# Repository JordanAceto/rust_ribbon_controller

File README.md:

# Rust Language STM32L412 Ribbon Controller

## Features

### Three analog outputs
- `RIBBON CV`: 1volt/per octave scaled control voltage generated by the main ribbon
- `GATE`: 5 volt gate signal which is high when pressing the main ribbon and low otherwise
- `MOD CV`: mod-wheel like control voltage generated by the MOD ribbon, in `[0v, +5v]` 

### MIDI output
- Note on/off based on finger position on the ribbon
- Pitch-bend message bends the pitch when the ribbon is in between notes 
- Mod: mod-wheel message generated by the MOD ribbon

### Three pitch modes are available
1) `QUANTIZE`: notes are forced to be musical half steps, sliding around will zipper to new notes
2) `ASSIST`: when you first press a new note it is forced to be a musical half step, but continued sliding is smooth
3) `SMOOTH`: no quantization is performed, offers the greatest degree of pitch freedom but is difficult to play in tune

### Glide control
- Adds portamento to the `RIBBON CV` signal
- This allows you to smooth out the steps when in `QUANTIZE` mode

### Notes about the MIDI output
- This software assumes that the pitch bend range on the receiving instrument is set to +/- 2 semitones (this is typically the default)
    - If the Assist or Smooth modes seem crazy, make sure that the pitch bend range on your instrument is set to +/- 2 semitones
- The MIDI output signal sends note-on, note-off, and pitch bend messages to generate the smooth ribbon action
    - This works best with a mono instrument, and may act differently depending on the MIDI implementation of the receiving device
    - If the receiving instrument has non-retriggering envelopes, it will smoothly slide as expected
    - If the instrument has retriggering envelopes, each time you slide into a new note the envelopes will be triggered
- The MIDI output starts on a fairly low note
    - It works best if the instrument being controlled can be transposed to different octaves

### Rear panel IO jacks and controls
- Output jacks for analog signals `RIBBON CV`, `MOD CV`, and `GATE`
- Standard `MIDI OUT` 5 pin DIN output jack
- `MIDI CH` channel select rotary switch
    - MIDI output is sent on the channel set here
- `9VDC IN` power supply input jack

## Calibration
- A trim potentiometer is exposed through a small hole so the device may be calibrated without disassembly
- Measure the `RIBBON CV` signal with a multimeter
- Set the `MODE` switch to `QUANTIZE`
- Adjust the trim potentiometer while playing alternating octaves so that the octaves are as close to 1.000v apart as you can get
- The `MOD CV` and MIDI output do not require calibration

## Power supply
- A common guitar-pedal style center-negative 9 volt DC wall wart powers the device
- The circuit consumes approximately 20mA from the 9 volt DC power supply

## Project status
- A prototype has been built and tested
- A handmade wooden body houses the components and provides a comfortable wrist rest while playing

## Project goals
- Mostly just for fun and to explore embedded Rust
- Serve as a test bed for the [Josh Ox Ribbon Synth](https://github.com/JordanAceto/josh_Ox_ribbon_synth)
- Build a cute little CV and MIDI source

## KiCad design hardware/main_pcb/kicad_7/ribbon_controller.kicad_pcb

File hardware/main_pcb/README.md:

# main_pcb

## ribbon_controller

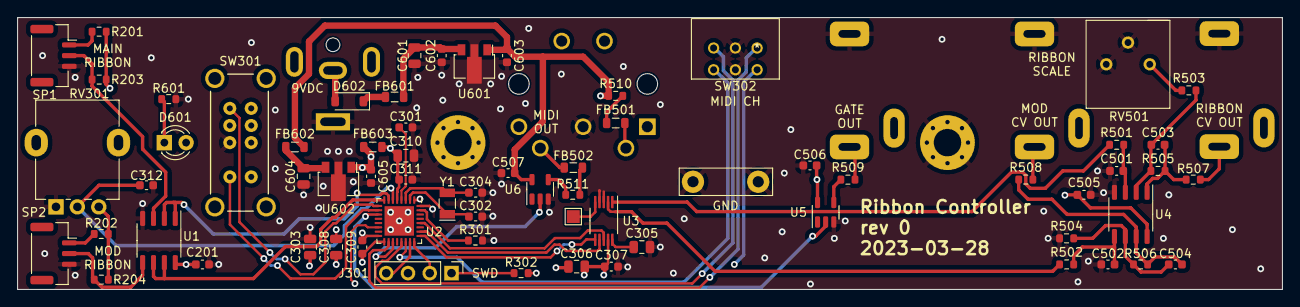
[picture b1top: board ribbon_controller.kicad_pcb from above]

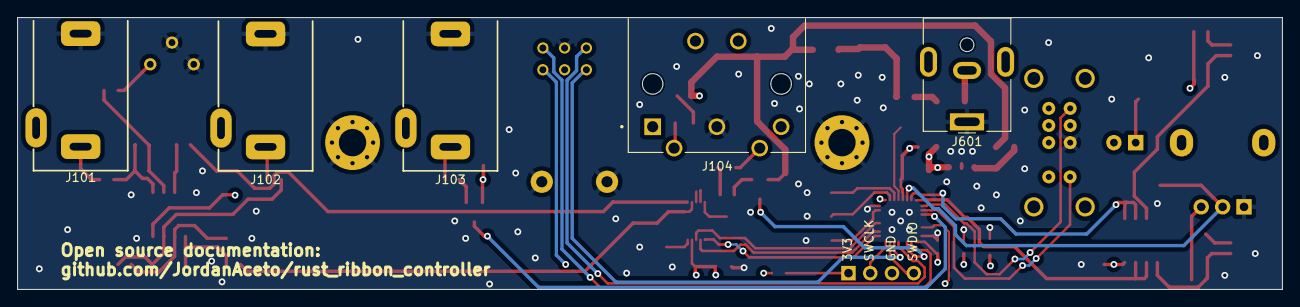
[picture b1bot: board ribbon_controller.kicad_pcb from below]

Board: 4 copper layers, 147.7 x 31.8 mm, 75 parts (5 on the bottom side), 54 nets.

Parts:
C201, C301, C307, C309, C311, C312, C501, C502, C503, C504, C505, C506, C507, C602, C603, C605: 100n; C_0603_1608Metric
C302, C304: 4p3; C_0603_1608Metric
C303: 10u; C_0805_2012Metric
C305, C306, C308, C310: 1u; C_0805_2012Metric
C601, C604: 2u2; C_0805_2012Metric
D601: XLMDK65D; LED_D3.0mm
D602: B5819W; D_SOD-123
FB501, FB502: 600R @ 100MHz; L_0805_2012Metric
FB601, FB602, FB603: 100R @ 100MHz; L_0805_2012Metric
H601, H602: MountingHole_Pad; MountingHole_3.2mm_M3_Pad_Via
J101, J102, J103: PJ302M
J104: CUI_SDF-50J
J301: SWD_header; PinHeader_1x04_P2.54mm_Vertical
J601: CUI_PJ-063AH; BarrelJack_CUI_PJ-063AH_Horizontal
R201, R202, R301, R501, R502, R504, R505, R506, R601: 10k; R_0603_1608Metric
R203, R204: 1M; R_0603_1608Metric
R302, R507, R510, R511: 220; R_0603_1608Metric
R503: 9k1; R_0603_1608Metric
R508, R509: 1k; R_0603_1608Metric
RV301: 10k; Potentiometer_Alpha_RD901F-40-00D_Single_Vertical
RV501: 2k; Potentiometer_Bourns_3296P_Horizontal
SP1: 400mm_softpot; JST_GH_SM03B-GHS-TB_1x03-1MP_P1.25mm_Horizontal
SP2: 50mm_softpot; JST_GH_SM03B-GHS-TB_1x03-1MP_P1.25mm_Horizontal
SW301: E-Switch_EG2301
SW302: nidec_SD-1011; SD-1011
TP401: ~{CLR}; TestPoint_Pad_1.5x1.5mm
TP601: GND; TestPoint_Bridge_Pitch7.62mm_Drill1.3mm
U1, U4: MCP6002-xSN; SO-8_3.9x4.9mm_P1.27mm
U2: STM32L412K8Ux; QFN-32-1EP_5x5mm_P0.5mm_EP3.45x3.45mm
U3: DAC8162xDGSx; VSSOP-10_3x3mm_P0.5mm
U5, U6: SN74LV1T34DBV; SOT-23-5
U601: L78L05_SOT89; SOT-89-3
U602: L78L33_SOT89; SOT-89-3
Y1: 32_768KHZ; Crystal_SMD_MicroCrystal_CC7V-T1A-2Pin_3.2x1.5mm

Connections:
+3.3V: C303.1, C306.1, C307.1, C308.1, C309.1, C605.1, FB603.1, R302.1, U2.1 (VDD), U2.17 (VDD), U3.9 (AVDD), U602.1 (OUT)
+3.3VA: C201.1, C310.1, C311.1, FB603.2, R201.1, R202.1, R203.1, R204.1, RV301.3, U1.8 (V+), U2.5 (VDDA)
+5V: C505.1, C506.1, C507.1, C603.1, FB602.1, R510.1, U4.8 (V+), U5.5 (VCC), U6.5 (VCC), U601.1 (OUT)
+9V: C601.1, C602.1, FB601.2, U601.3 (IN)
/DAC/MOD_CV_2V5: R502.1, U3.2 (VOUTB)
/DAC/RIBBON_CV_2V5: R501.1, U3.1 (VOUTA)
/DAC/SPI_CS: U2.25 (PA15), U3.6 (~SYNC)
/DAC/SPI_SCK: U2.26 (PB3), U3.7 (SCLK)
/DAC/SPI_SDO: U2.28 (PB5), U3.8 (DIN)
/input_buffers/MAIN_RIB_RAW_V: U1.1, U1.2 (-), U2.7 (PA1)
/input_buffers/MOD_RIB_RAW_V: U1.6 (-), U1.7, U2.8 (PA2)
/microcontroller/GATE_3V3: U2.11 (PA5), U5.2 (A)
/microcontroller/GLIDE_CV: C312.1, RV301.2, U2.6 (PA0)
/microcontroller/MIDI_CH_1: SW302.1, U2.18 (PA8)
/microcontroller/MIDI_CH_2: SW302.2, U2.22 (PA12)
/microcontroller/MIDI_CH_4: SW302.4, U2.21 (PA11)
/microcontroller/MIDI_CH_8: SW302.8, U2.14 (PB0)
/microcontroller/MIDI_TX_3V3: U2.19 (PA9), U6.2 (A)
/microcontroller/MODE_SW_1: SW301.1, U2.9 (PA3)
/microcontroller/MODE_SW_2: SW301.4, U2.10 (PA4)
/microcontroller/SYS_SWCLK: J301.2, U2.24 (PA14)
/microcontroller/SYS_SWDIO: J301.4, U2.23 (PA13)
/output_buffers/GATE_5V: J103.T, R509.2
/output_buffers/MIDI_OUT_P4: FB501.2, J104.4
/output_buffers/MIDI_OUT_P5: FB502.2, J104.5
/output_buffers/MOD_CV_5V: J102.T, R508.2
/output_buffers/RIBBON_CV_FINAL: J101.T, R507.2
GND: C201.2, C301.1, C302.1, C303.2, C304.1, C305.2, C306.2, C307.2, C308.2, C309.2, C310.2, C311.2, C312.2, C501.1, C502.1, C505.2, C506.2, C507.2, C601.2, C602.2, C603.2, C604.2, C605.2, H601.1, H602.1, J101.S, J102.S, J103.S, J104.2, J301.3, J601.1, R301.1, R504.1, R601.1, RV301.1, RV501.2, RV501.3, SP1.3, SP2.3, SW301.3, SW302.C, TP601.1, U1.4 (V-), U2.16 (VSS), U2.32 (VSS), U2.33 (VSS), U3.3 (GND), U3.4 (~LDAC), U4.4 (V-), U5.3 (GND), U6.3 (GND), U601.2 (GND), U602.2 (GND)
unnamed: C503.2, R505.2, R507.1, U4.1
unnamed: C504.2, R506.2, R508.1, U4.7
unnamed: D601.2 (A), D602.2 (A), J601.2
unnamed: D601.1 (K), R601.2
unnamed: D602.1 (K), FB601.1
unnamed: FB501.1, R510.2
unnamed: FB502.1, R511.2
unnamed: J301.1, R302.2
unnamed: R201.2, SP1.1
unnamed: R202.2, SP2.1
unnamed: R503.1, RV501.1
unnamed: R203.2, SP1.2, U1.3 (+)
unnamed: R204.2, SP2.2, U1.5 (+)
unnamed: C301.2, U2.4 (NRST)
unnamed: C302.2, U2.2 (PC14), Y1.1
unnamed: C304.2, U2.3 (PC15), Y1.2
unnamed: R301.2, U2.31 (PH3)
unnamed: C305.1, U3.10 (VREFH/VREFOUT)
unnamed: TP401.1, U3.5 (~CLR)
unnamed: C501.2, R501.2, U4.3 (+)
unnamed: C503.1, R503.2, R505.1, U4.2 (-)
unnamed: C502.2, R502.2, U4.5 (+)
unnamed: C504.1, R504.2, R506.1, U4.6 (-)
unnamed: R509.1, U5.4 (Y)
unnamed: R511.1, U6.4 (Y)
unnamed: C604.1, FB602.2, U602.3 (IN)

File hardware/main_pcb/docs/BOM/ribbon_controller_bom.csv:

"#","Reference","Qty","Value","Footprint","DNP"
"1","C201, C301, C307, C309, C311, C312, C501, C502, C503, C504, C505, C506, C507, C602, C603, C605","16","100n","Capacitor_SMD:C_0603_1608Metric",""
"2","C302, C304","2","4p3","Capacitor_SMD:C_0603_1608Metric",""
"3","C303","1","10u","Capacitor_SMD:C_0805_2012Metric",""
"4","C305, C306, C308, C310","4","1u","Capacitor_SMD:C_0805_2012Metric",""
"5","C601, C604","2","2u2","Capacitor_SMD:C_0805_2012Metric",""
"6","D601","1","XLMDK65D","LED_THT:LED_D3.0mm",""
"7","D602","1","B5819W","Diode_SMD:D_SOD-123",""
"8","FB501, FB502","2","600R @ 100MHz","Inductor_SMD:L_0805_2012Metric",""
"9","FB601, FB602, FB603","3","100R @ 100MHz","Inductor_SMD:L_0805_2012Metric",""
"10","H601, H602","2","MountingHole_Pad","MountingHole:MountingHole_3.2mm_M3_Pad_Via",""
"11","J101, J102, J103","3","PJ302M","custom_footprints:PJ302M",""
"12","J104","1","CUI_SDF-50J","custom_footprints:CUI_SDF-50J",""
"13","J301","1","SWD_header","Connector_PinHeader_2.54mm:PinHeader_1x04_P2.54mm_Vertical",""
"14","J601","1","CUI_PJ-063AH","Connector_BarrelJack:BarrelJack_CUI_PJ-063AH_Horizontal",""
"15","R201, R202, R301, R501, R502, R504, R505, R506, R601","9","10k","Resistor_SMD:R_0603_1608Metric",""
"16","R203, R204","2","1M","Resistor_SMD:R_0603_1608Metric",""
"17","R302, R507, R510, R511","4","220","Resistor_SMD:R_0603_1608Metric",""
"18","R503","1","9k1","Resistor_SMD:R_0603_1608Metric",""
"19","R508, R509","2","1k","Resistor_SMD:R_0603_1608Metric",""
"20","RV301","1","10k ","custom_footprints:Potentiometer_Alpha_RD901F-40-00D_Single_Vertical",""
"21","RV501","1","2k","custom_footprints:Potentiometer_Bourns_3296P_Horizontal",""
"22","SP1","1","400mm_softpot","Connector_JST:JST_GH_SM03B-GHS-TB_1x03-1MP_P1.25mm_Horizontal",""
"23","SP2","1","50mm_softpot","Connector_JST:JST_GH_SM03B-GHS-TB_1x03-1MP_P1.25mm_Horizontal",""
"24","SW301","1","E-Switch_EG2301","custom_footprints:E-Switch_EG2301",""
"25","SW302","1","nidec_SD-1011","custom_footprints:SD-1011",""
"26","TP401","1","~{CLR}","TestPoint:TestPoint_Pad_1.5x1.5mm",""
"27","TP601","1","GND","TestPoint:TestPoint_Bridge_Pitch7.62mm_Drill1.3mm",""
"28","U1, U4","2","MCP6002-xSN","Package_SO:SO-8_3.9x4.9mm_P1.27mm",""
"29","U2","1","STM32L412K8Ux","Package_DFN_QFN:QFN-32-1EP_5x5mm_P0.5mm_EP3.45x3.45mm",""
"30","U3","1","DAC8162xDGSx","Package_SO:VSSOP-10_3x3mm_P0.5mm",""
"31","U5, U6","2","SN74LV1T34DBV","Package_TO_SOT_SMD:SOT-23-5",""
"32","U601","1","L78L05_SOT89","Package_TO_SOT_SMD:SOT-89-3",""
"33","U602","1","L78L33_SOT89","Package_TO_SOT_SMD:SOT-89-3",""
"34","Y1","1","32_768KHZ","Crystal:Crystal_SMD_MicroCrystal_CC7V-T1A-2Pin_3.2x1.5mm",""

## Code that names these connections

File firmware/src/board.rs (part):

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        // Gate pin
        //
        ////////////////////////////////////////////////////////////////////////
        let gate_pin = gpioa.pa5.into_push_pull_output_in_state(
            &mut gpioa.moder,
            &mut gpioa.otyper,
            PinState::Low,
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
        // gpio pins which are configured as analog inputs on the physical PCB
        let mut adc_pins = (
            gpioa.pa0.into_analog(&mut gpioa.moder, &mut gpioa.pupdr),
            gpioa.pa1.into_analog(&mut gpioa.moder, &mut gpioa.pupdr),
            gpioa.pa2.into_analog(&mut gpioa.moder, &mut gpioa.pupdr),
        );
        adc1.configure_sequence(&mut adc_pins.0, Sequence::One, SampleTime::Cycles640_5);
        adc1.configure_sequence(&mut adc_pins.1, Sequence::Two, SampleTime::Cycles640_5);
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        }

        let tx_pin = gpioa
            .pa9
            .into_alternate(&mut gpioa.moder, &mut gpioa.otyper, &mut gpioa.afrh);
        let rx_pin =
            gpioa
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        //
        ////////////////////////////////////////////////////////////////////////
        let sck = gpiob
            .pb3
            .into_alternate(&mut gpiob.moder, &mut gpiob.otyper, &mut gpiob.afrl);
        let sdi = gpiob
            .pb4
            .into_alternate(&mut gpiob.moder, &mut gpiob.otyper, &mut gpiob.afrl);
        let sdo = gpiob
            .pb5
            .into_alternate(&mut gpiob.moder, &mut gpiob.otyper, &mut gpiob.afrl);

        let mut nss = gpioa.pa15.into_push_pull_output_in_state(
            &mut gpioa.moder,
            &mut gpioa.otyper,
            PinState::High,
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        ////////////////////////////////////////////////////////////////////////
        let mode_switch = (
            gpioa
                .pa3
                .into_pull_up_input(&mut gpioa.moder, &mut gpioa.pupdr),
            gpioa
                .pa4
                .into_pull_up_input(&mut gpioa.moder, &mut gpioa.pupdr),
        );

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        ////////////////////////////////////////////////////////////////////////
        let midi_ch_switch = (
            gpioa
                .pa8
                .into_pull_up_input(&mut gpioa.moder, &mut gpioa.pupdr),
            gpioa
                .pa12
                .into_pull_up_input(&mut gpioa.moder, &mut gpioa.pupdr),
            gpioa
                .pa11
                .into_pull_up_input(&mut gpioa.moder, &mut gpioa.pupdr),
            gpiob
                .pb0
                .into_pull_up_input(&mut gpiob.moder, &mut gpiob.pupdr),
        );

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/// Pins which may be read by the ADC are represented here
#[derive(Clone, Copy)]
pub enum AdcPin {
    PA0 = 0,
    PA1 = 1,
    PA2 = 2,
}

/// Channels of the onboard DAC are represented here
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
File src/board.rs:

use stm32l0xx_hal::{
    adc::{Adc, Ready},
    delay::Delay,
    gpio::{
        gpioa::{PA0, PA4, PA5, PA7, PA9},
        gpioc::{PC14, PC15},
        Analog, Input, Output, PullUp, PushPull,
    },
    pac::{Peripherals, ADC, SPI1},
    prelude::*,
    rcc, serial,
    spi::{NoMiso, Spi, MODE_0},
};

use nb::block;

/// The physical board hardware structure is represented here.
///
/// The board consists of digital and analog peripherals.
pub struct Board {
    /// The analog to digital converter
    adc: Adc<Ready>,

    /// The pin used to read analog signals via the ADC
    adc_pin: PA0<Analog>,

    /// GPIO pin used as a gate ouptut
    gate_pin: PA9<Output<PushPull>>,

    mode_switch_1: PC14<Input<PullUp>>,
    mode_switch_2: PC15<Input<PullUp>>,

    /// SPI peripheral for writing to onboard DAC
    spi: Spi<SPI1, (PA5<Analog>, NoMiso, PA7<Analog>)>,
    /// SPI chip select pin
    nss: PA4<Output<PushPull>>,

    /// The USART
    tx: serial::Tx<serial::USART2>,

    delay: Delay,
}

/// The channels of the MCP4822 DAC are represented here.
#[derive(Clone, Copy)]
pub enum Mcp4822Channel {
    A = 0,
    B = 1,
}

impl Board {
    /// `Board::init()` is the board with all necessary peripherals initialized.
    pub fn init() -> Self {
        // general peripheral housekeeping
        let dp = Peripherals::take().unwrap();
        let cp = cortex_m::Peripherals::take().unwrap();
        let mut rcc = dp.RCC.freeze(rcc::Config::hsi16());
        let gpioa = dp.GPIOA.split(&mut rcc);
        let gpioc = dp.GPIOC.split(&mut rcc);

        // mode switch pins
        let mode_switch_1 = gpioc.pc14.into_pull_up_input();
        let mode_switch_2 = gpioc.pc15.into_pull_up_input();

        // USART for MIDI output
        let tx_pin = gpioa.pa2;
        let rx_pin = gpioa.pa3;

        let usart = dp
            .USART2
            .usart(
                tx_pin,
                rx_pin,
                serial::Config {
                    baudrate: 31_250_u32.Bd(), // MIDI baud rate
                    wordlength: serial::WordLength::DataBits8,
                    parity: serial::Parity::ParityNone,
                    stopbits: serial::StopBits::STOP1,
                },
                &mut rcc,
            )
            .unwrap();

        let (tx, _) = usart.split();

        // ADC
        let adc = dp.ADC.constrain(&mut rcc);
        let adc_pin = gpioa.pa0.into_analog();
        // configure hardware oversampling for effective ADC resolution of 16 bits
        unsafe {
            (*ADC::ptr()).cfgr2.modify(|_, w| {
                w.ovsr().mul256();
                w.ovss().bits(4);
                w.ovse().enabled()
            });
        }

        // SPI DAC
        let mut nss = gpioa.pa4.into_push_pull_output();
        nss.set_high().unwrap();
        let sck = gpioa.pa5;
        let mosi = gpioa.pa7;

        let spi = dp
            .SPI1
            .spi((sck, NoMiso, mosi), MODE_0, 100_000.Hz(), &mut rcc);

        // GATE PIN
        let gate_pin = gpioa.pa9.into_push_pull_output();

        let delay = cp.SYST.delay(rcc.clocks);

        Self {
            adc,
            adc_pin,
            gate_pin,
            mode_switch_1,
            mode_switch_2,
            spi,
            nss,
            tx,
            delay,
        }
    }

    /// `board.sleep_ms(ms)` causes the board to busy-wait for the `ms` milliseconds
    pub fn sleep_ms(&mut self, ms: u16) {
        self.delay.delay_ms(ms);
    }

    /// `board.serial_write(val)` writes the byte `val` via the USART in a blocking fashion
    pub fn serial_write(&mut self, val: u8) {
        block!(self.tx.write(val)).ok();
    }

    /// `board.get_raw_adc()` is the current value of the ADC.
    pub fn get_raw_adc(&mut self) -> u16 {
        self.adc.read(&mut self.adc_pin).unwrap()
    }

    /// `board.get_mode_switch_1()` is the current state of mode switch 1
    pub fn get_mode_switch_1(&self) -> bool {
        self.mode_switch_1.is_low().unwrap()
    }

    /// `board.get_mode_switch_2()` is the current state of mode switch 2
    pub fn get_mode_switch_2(&self) -> bool {
        self.mode_switch_2.is_low().unwrap()
    }
    /// `board.mcp4822_write(val_u12, channel)` writes the 12 bit value to the given channel of the onboard MCP4822 DAC.
    ///
    /// # Arguments:
    ///
    /// * `val_u12` - The 12 bit unsigned value to write. Bits above 11 are trucated.
    ///
    /// * `channel` - The enumerated MCP4822 channel
    pub fn mcp4822_write(&mut self, val_u12: u16, channel: Mcp4822Channel) {
        let low_word = (val_u12 & 0xFF) as u8;

        // OR in the channel, GAIN=1x, and Enable Vout
        let high_word = (((val_u12 & DAC_MAX) >> 8) as u8) | ((channel as u8) << 7) | 0b00110000;

        self.nss.set_low().unwrap();
        self.spi.write(&[high_word, low_word]).unwrap();
        self.nss.set_high().unwrap();
    }

    /// `board.set_gate(val)` sets the state of the gate pin to `val`.
    pub fn set_gate(&mut self, val: bool) {
        match val {
            true => self.gate_pin.set_high().unwrap(),
            false => self.gate_pin.set_low().unwrap(),
        }
    }
}

/// The maximum value that can be produced by the Analog to Digital Converters.
pub const ADC_MAX: u16 = u16::MAX;

/// The maximum value that can be written to the onboard Digital to Analog Converter.
pub const DAC_MAX: u16 = 0x0FFF;

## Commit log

2022-12-21 Add license
2022-12-22 Enable ADC hardware oversampling for 16 bit resolution
2022-12-23 Move structs and impls above constants
2022-12-25 Add SPI DAC
2022-12-26 Add Quantizer module
2023-02-12 Ignore kicad backup folders
2023-02-12 Add very basic MIDI functionality, change how quantizer works
2023-02-12 Add kicad7 files so we can tweak the schematic snippet with new changes
2023-02-12 Update comments to match new reality
2023-02-14 Make MIDI ribbon play in-tune half steps when you first press down
2023-02-14 Add mode switch with 3 MIDI note modes
2023-02-14 Remove old testing comments, add function docstrings for board switch fcs
2023-02-14 Use gate signal instead of testing signal for GPIO gate
2023-04-11 Massive project overhaul, use STM32L412 uC, fab circuit boards
2023-04-11 Add MIDI mod-wheel code
2023-04-12 Design jack plate
2023-04-12 Add renders of proposed wooden body, update main README
2023-04-15 Use crates as dependencies instead of github repos
2023-04-15 Add measured current draw to README
2023-04-15 Tweak SPI DAC so that Vref turns on reliably
2023-05-24 Enable LSE clk to auto trim HSI clk
2023-05-24 Move JLC placeholder text silkscreen out of mounting hole
2023-05-24 Add photo of finished device, rename images, update main README
2023-05-25 Add notes about MIDI implementation to main README

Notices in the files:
hardware/main_pcb/kicad_7/ribbon_controller.kicad_pcb:
creativecommons.org/licenses/by/4.0
license: CC by 4.0
